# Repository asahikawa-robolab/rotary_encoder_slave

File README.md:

# 概要
モータやエンコーダを使用するのに必要なプログラムをまとめたリポジトリ．下記のプログラムはすべて同一の基板で使用可能．
|プログラム|用途|
|:-|:-|
|pwm_control|デューティー比でモータを制御する|
|revolution_control|回転数でモータを制御する|
|rotation_angle_control|回転角でモータを制御する|
|odometry|接地エンコーダからオドメトリを取得する|
# リファレンス
* [pwm_control](doc/pwm_control.md)
* [revolution_control](doc/revolution_control.md)
* [rotation_angle_control](doc/rotation_angle_control.md)
* [odometry](doc/odometry.md)
# リポジトリ構成
```tree
├── circuit
│   ├── new -> 新版の基板データ ( eagle )
│   └── old -> 旧版の基板データ ( pcbe )
└── program
    ├── odometry.X ---------------> odometry のプログラム
    ├── pwm_control.X ------------> pwm_control のプログラム
    ├── revolution_control.X -----> revolution_control のプログラム
    └── rotation_angle_control.X -> rotation_angle_control のプログラム
```

# 動作確認環境
* IDE : MPLAB X IDE v4.15
* コンパイラ : XC16 v1.41
* コンパイルオプション : -std=c99
    * File -> Project Properties -> Categories: -> Conf: [default] -> XC16(Global Options) -> xc16-gcc -> Additional options: で指定

# 基板の使用方法
# LEDについて
* 受信ができているときは高速で点滅する
* プログラムの実行中に深刻なエラーが発生したときは一定間隔で点滅する

# 回転量の符号について
* 本リポジトリのプログラムで登場する，「デューティー比，位置カウント，回転角，回転数」の符号は右ねじの法則に従っている．***モータ本体から軸に向かう向きに親指を向けたときの回転方向を正***と定義する．また，***正の方向に回転することを正転***と定義する．
* pwm_control を使って正のデューティ比でモータを駆動したとき，モータが正転しない場合はモータにはんだ付けされている線を入れ替えて回転方向を逆転させなければならない．
* モータの回転方向を逆転させるために，***プログラムで MD に出力する IO ピンを入れ替えないこと．*** 先のことを考えなければこれが一番簡単な方法だが，そのモータを使うときだけ他とは違うプログラムを使わなければならないことになる．これは経験上非常に面倒．

# QEI モジュールについて
* ***QEI ( Quadrature Encoder Interface)*** とは日本語で「直交エンコーダインターフェース」のことであり，端的に言えばエンコーダの信号をマイコンに読み込むためのモジュールである．
* 専用の回路を用意してハードウェアで処理しているタイプと，ソフトウェアで疑似的に QEI を実装しているタイプの２つがある．
* 後者のタイプはマイコンの処理が重くなると処理可能な周波数が下がってしまうため，***ハードウェアで実装されている QEI の使用を強く推奨する．***
* ピン変化割り込みを使用することで QEI モジュールを疑似的に実装することはできるが，処理可能な周波数が低すぎて使い物にならなかった．
### 参考
* [セクション 15. 直交エンコーダ インターフェイス(QEI)](http://ww1.microchip.com/downloads/jp/DeviceDoc/70208B_JP.pdf)

# 使用上の注意
# トラブルシューティング

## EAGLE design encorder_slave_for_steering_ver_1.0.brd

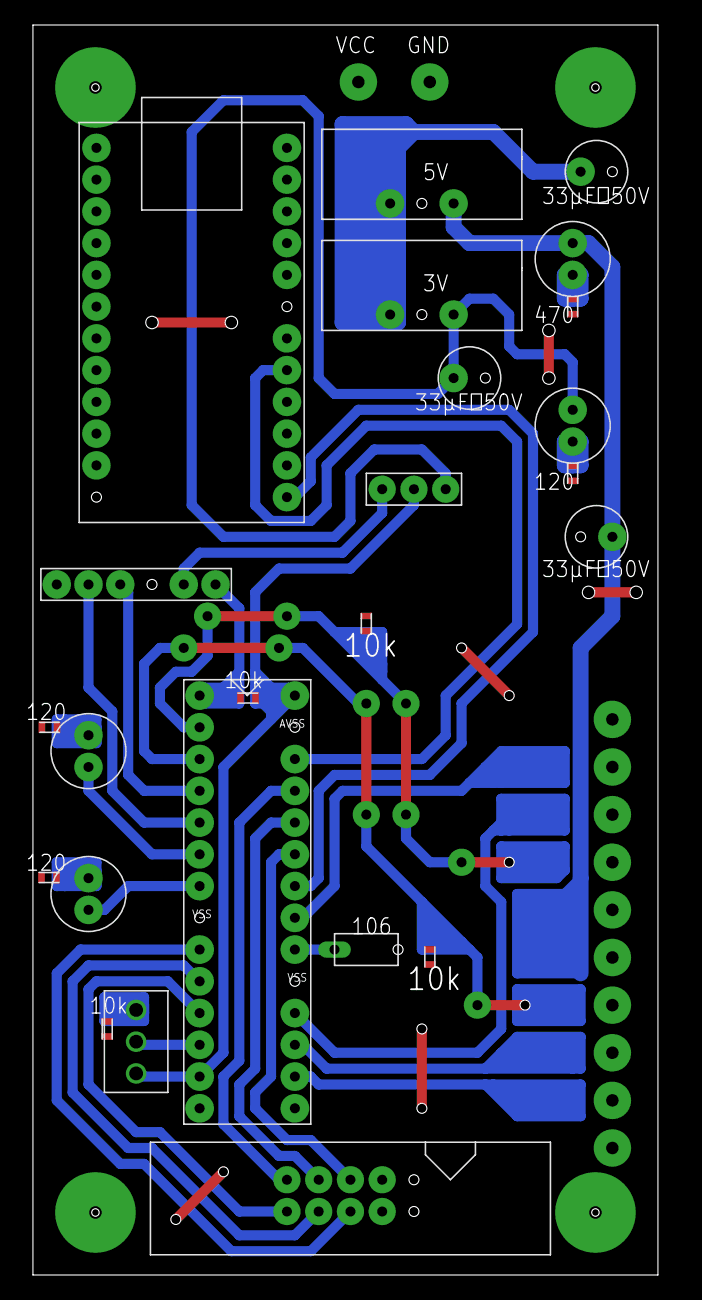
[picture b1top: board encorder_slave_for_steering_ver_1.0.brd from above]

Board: 2 copper layers, 52.1 x 100.0 mm, 24 parts (0 on the bottom side), 19 nets.

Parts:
E$1: WRITER
E$2: CAPACITORS_106
E$3: SERIALCOM
E$4, E$16, E$17, E$18: LED
E$5: TOGGLE_SWITCH(3PIN)
E$6, E$19: CHIP_RESISTOR
E$7, E$8: REGULATOR
E$10: 3PINSWITCH
E$12: RIBBON_CABLE
E$13: PIC_28P_2
E$14, E$15, E$20: CAPACITOR_33
U$1, U$2, U$16, U$17, U$21, U$22: CHIP_RESISTOR

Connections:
S$1: E$2.P$2, E$13.VCAP
S$3: E$1.P$5, E$13.RB1
S$4: E$1.P$4, E$13.RB0
S$5: E$12.P$5, E$13.RA4
S$6: E$12.P$6, E$13.RA3
S$7: E$12.P$7, E$13.RA2
S$10: E$12.P$1, E$13.RB14
S$12: E$5.P$1, E$10.P$2, E$13.AVDD, E$13.VDD
S$13: E$5.P$2, E$13.RB4
S$14: E$13.RB3, E$16.P$1
S$19: E$12.P$2, E$13.RB13
S$20: E$12.P$3, E$13.RB12
S$21: E$13.RB2, E$18.P$1
S$22: E$1.P$2, E$10.P$1
S$57: E$1.P$1, E$13.MCLR
S$70: E$3.P$9, E$13.RB15
S$78: E$3.P$17, E$13.RB11
S$82: E$7.P$3, E$15.P$1, E$17.P$1
S$84: E$4.P$2, E$8.P$3, E$10.P$3, E$14.P$1

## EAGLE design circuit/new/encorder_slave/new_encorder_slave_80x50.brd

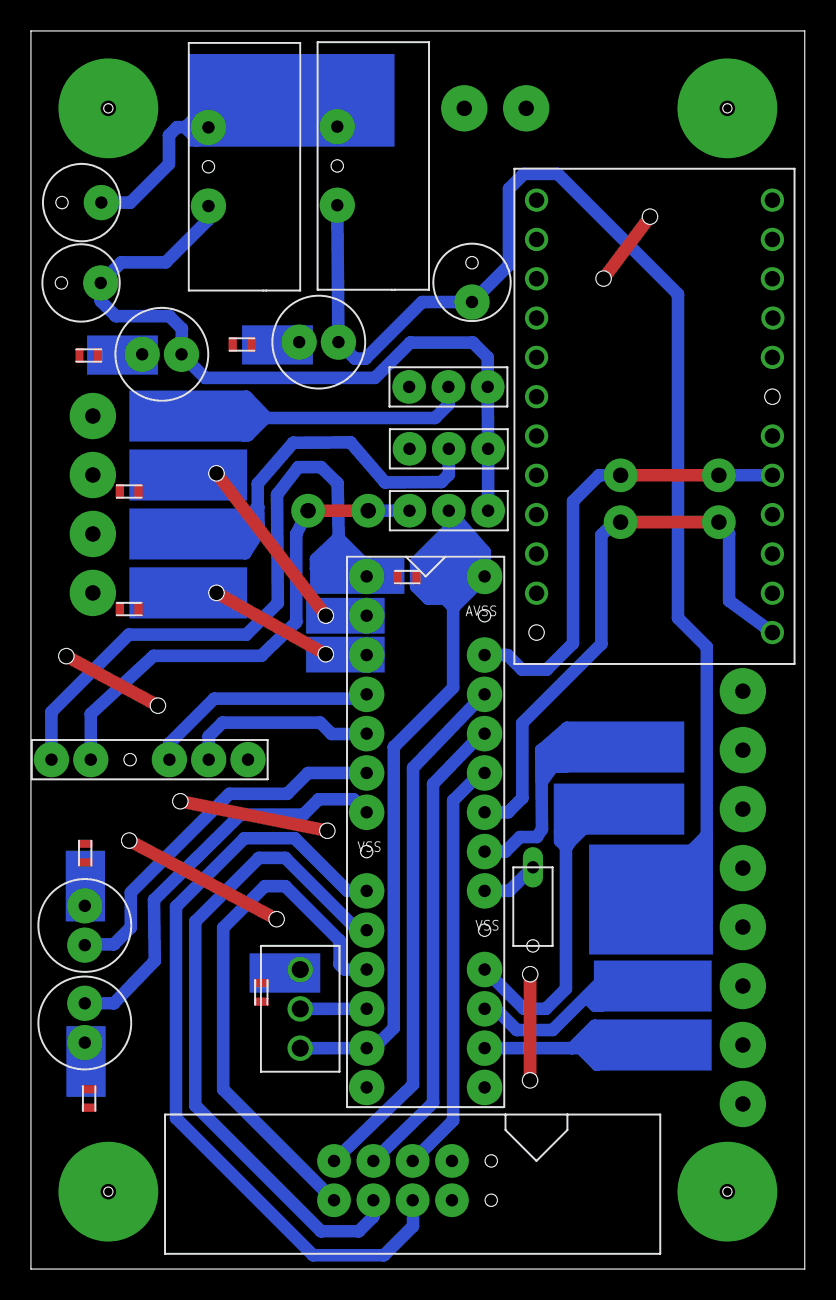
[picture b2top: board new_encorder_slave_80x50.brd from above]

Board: 2 copper layers, 50.0 x 80.0 mm, 26 parts (0 on the bottom side), 17 nets.

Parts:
DSPIC33FJ128MC1: DSPIC33FJ128MC; PIC_28P_2
U$1, U$2, U$3, U$4: LED
U$5, U$16, U$17, U$18, U$19, U$20, U$21, U$23: CHIP_RESISTOR
U$6: TOGGLE_SWITCH(3PIN)
U$7: AE-UM232R
U$8: RIBBON_CABLE
U$9, U$10: REGULATOR
U$11: WRITER
U$12, U$13, U$14: CAPACITOR_33
U$15: CAPACITORS_106
U$24, U$25, U$26: 3PINSWITCH

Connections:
S$2: DSPIC33FJ128MC1.RB4, U$6.P$2
S$4: DSPIC33FJ128MC1.RB13, U$8.P$2
S$7: DSPIC33FJ128MC1.RB14, U$8.P$1
S$9: DSPIC33FJ128MC1.RA3, U$8.P$6
S$10: DSPIC33FJ128MC1.RA2, U$8.P$7
S$12: DSPIC33FJ128MC1.RA4, U$8.P$5
S$13: DSPIC33FJ128MC1.RB3, U$3.P$2
S$19: DSPIC33FJ128MC1.RB2, U$2.P$2
S$22: DSPIC33FJ128MC1.RB1, U$11.P$5
S$23: DSPIC33FJ128MC1.RB0, U$11.P$4
S$25: DSPIC33FJ128MC1.AVDD, DSPIC33FJ128MC1.VDD, U$6.P$1, U$24.P$2
S$26: DSPIC33FJ128MC1.MCLR, U$11.P$1
S$28: U$1.P$2, U$10.P$3, U$13.P$1
S$30: DSPIC33FJ128MC1.RB12, U$8.P$3
S$33: DSPIC33FJ128MC1.VCAP, U$15.P$2
S$41: U$4.P$1, U$9.P$3, U$12.P$1, U$24.P$3, U$25.P$3, U$26.P$3
S$56: U$9.P$2, U$14.P$1

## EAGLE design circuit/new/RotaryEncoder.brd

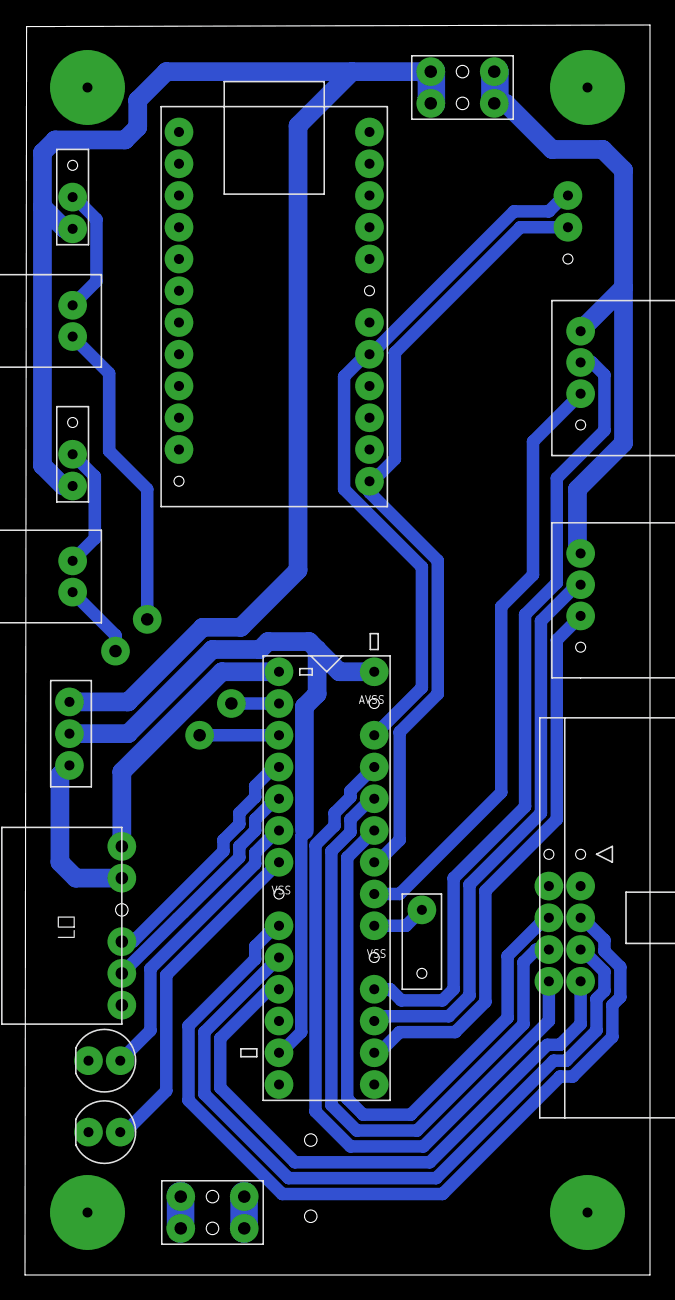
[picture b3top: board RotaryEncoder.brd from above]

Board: 2 copper layers, 50.0 x 100.0 mm, 19 parts (0 on the bottom side), 13 nets.

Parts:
CAPACITOR1: CAPACITOR_VCAP; CAPACITOR_1
CHIP_CAPACITOR1, CHIP_CAPACITOR2: CHIP_CAPACITOR
CHIP_REGISTER1: CHIP_REGISTER
DSPIC33FJ128MC1: DSPIC33FJ128MC; PIC_28P_2
E$1: HIF3BD-10PA
E$2, E$3: PINHEADER_2*3
E$4: SLIDE_SWITCH_3
E$5: USB_SERIAL(FT232RL)
LED1, LED2: LED_1
PICKIT1: PICKIT3_L_REVERSE
SLIDE_SWITCH4, SLIDE_SWITCH5: SLIDE_SWITCH_3_A_GND
XH_SIDE_P3, XH_SIDE_P4: XH_SIDE_P4; XH_SIDE_4P
XH_SIDE_P5, XH_SIDE_P6: XH_SIDE_2P

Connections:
unnamed: DSPIC33FJ128MC1.RB1, PICKIT1.5
unnamed: DSPIC33FJ128MC1.RB2, LED1.A
unnamed: DSPIC33FJ128MC1.RB3, LED2.A
unnamed: DSPIC33FJ128MC1.RB13, E$1.4
S$1: DSPIC33FJ128MC1.RB4, E$1.1
S$2: CAPACITOR1.+, DSPIC33FJ128MC1.VCAP
S$8: E$4.2, PICKIT1.2
S$10: DSPIC33FJ128MC1.RA2, E$1.5
S$11: DSPIC33FJ128MC1.RB0, PICKIT1.4
S$18: DSPIC33FJ128MC1.MCLR, PICKIT1.1
S$19: DSPIC33FJ128MC1.RB11, E$5.TXD
S$23: DSPIC33FJ128MC1.RB15, E$5.RXD
S$28: DSPIC33FJ128MC1.RA3, E$1.3

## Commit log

2020-02-06 2018 年全国大会終了直後
    [根本]回転数、回転角、接地エンコーダ用基板
    ・回転角制御用のリミットを追加
    ・リミットだけでなくレーザーでも使えるようにスイッチをつけています。
    [太田]GitHubに初アップロード
    ・回転数制御の完成版
    [太田]GitHubに初アップロード
2020-02-21 [地引] 分解しかけて組み立て直した B 手動ロボットに対応させた．
    ● 組み立てる際に逆向きに取り付けられた昇降機構のエンコーダに対応させた．
2020-03-14 2019 年全国大会終了直後
    [根本]回転数、回転角、接地エンコーダ用基板
    ・回転角制御用のリミットを追加
    ・リミットだけでなくレーザーでも使えるようにスイッチをつけています。
    [太田]GitHubに初アップロード
    ・回転数制御の完成版
    [太田]GitHubに初アップロード
2020-03-14 パラメータ設定に対応
    ◍ Raspberry Pi からパラメータを設定できるようにした
    ◍ README を追加
    [太田]基板の回路図を追加した
    [根本]Eagleで作った基板を追加
    ・Eagleで作った基板を追加
    [地引] ディレクトリを整理
2020-03-14 revolution_control のフローチャートを作成
2020-03-18 PARAM_ENABLE を追加
    ◍ pwm_control, revolution_control, rotation_angle_control に PARAM_ENABLE を追加．
    ◍ 受信割り込みでデバック LDE を点滅させるように変更．
    ◍ revolution_control と rotation_angle_control は一部パラメータの順番を入れ替えた．
    ◍ パラメータの並べ替えに対応させた
2020-03-18 odometry.md が完成
    ◍ QEI モジュールに関する補足説明を追加．
    ◍ pwm_control.md にフローチャートを追加．
    ◍ odometry に PARAM_ENCODER_POL の処理を実装．動作未確認．
    ◍ pwm_control にデューティー比の大きさを 100 以下に収める処理を追加．
2020-03-18 rev と rot のフローチャート，パラメータ詳細完成
2020-03-18 GET_SIGNAL で 0 除算が発生しないようにした
2020-03-18 pwm_conrtol の説明を追加
2020-03-24 additional_options の写真を修正
2020-08-31 pwm_control に加減速処理を実装
    commit 7756290a4ae4a987a20a9126475dee8c7837efc9
    Author: Takuto Jibiki <eipuuuuk825@gmail.com>
    Date: Mon Aug 31 16:57:51 2020 +0900
    マージする準備
    ◍ 加減速処理の動画を削除
    ◍ オートフォーマットをかけた
2020-08-31 pwm_control.md のパラメータに関する記述を変更
2020-09-26 [大平]pwmを計算する回数の訂正
    ・繰り返し回数が1のみだったため1chしか出力されない状況だった
2022-07-11 エラー停止機能有効/無効切り替え機能の追加
    ・停止PWMを超えた場合に停止せずに最大PWMを出力し続ける機能を追加．
    ・その場合でもエンコーダーの極性エラーもチェックする．
    ・従来との切り替えのためのパラメータ追加
2022-07-28 pwmの値が非数だったら0 にするように変更
    ・駆動をONにした後にエンコーダースレーブを起動した時に暴走するバグを修正
2022-08-01 エンコーダーの値がおかしければ無視するように変更
2022-08-02 eagle用の基板データの追加
2022-08-02 基板が間違っていたため上げなおし
2022-10-09 変更 ・rpmの上限のパラメータを追加して外れ値が入ると無視するように変更
2023-04-18 Update revolution_control.md
    mdファイルのMaxRPMの説明の追加
2023-05-20 独ステ用
2023-05-22 バグってたので修正
2023-05-23 PID制御の追加
2023-05-26 ディレクトリ構成がきもかったので修正
2023-05-26 エンコーダーエラー停止機能の無効化のパラメーターを追加
2023-05-26 LAP制御のMD用
2023-07-18 Update main.c
    0点の振幅を30msから18msに変更
2023-08-09 回転数を送るように変更
